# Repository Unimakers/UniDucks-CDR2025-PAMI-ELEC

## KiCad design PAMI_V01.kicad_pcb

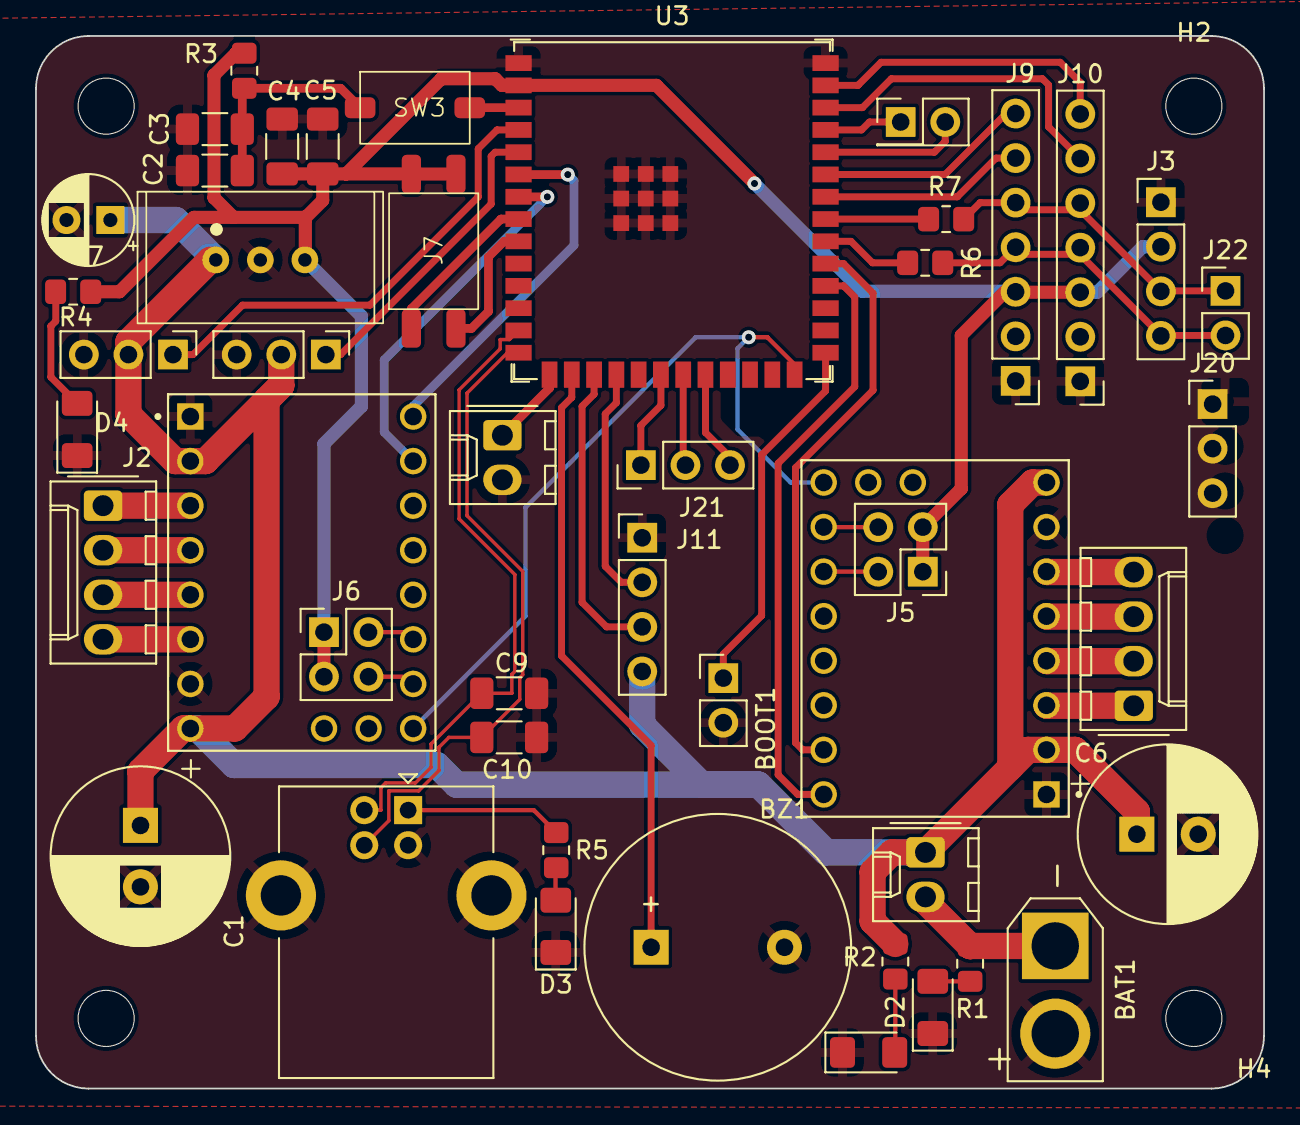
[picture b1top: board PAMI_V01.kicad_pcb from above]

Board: 2 copper layers, 70.0 x 60.0 mm, 50 parts (0 on the bottom side), 52 nets.

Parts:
BAT1: Conn; AMASS_XT30U-F_1x02_P5.0mm_Vertical
BOOT1: Conn; PinHeader_1x02_P2.54mm_Vertical
BZ1: Buzzer; Buzzer_15x7.5RM7.6
C1, C6: 100uF; CP_Radial_D10.0mm_P3.50mm
C2, C5: 0.1uF; C_1206_3216Metric_Pad1.33x1.80mm_HandSolder
C3, C9, C10: TBD; C_1206_3216Metric_Pad1.33x1.80mm_HandSolder
C4: 22uF; C_1206_3216Metric_Pad1.33x1.80mm_HandSolder
C7: 10uF; CP_Radial_D5.0mm_P2.50mm
D1, D2, D3, D4: LED_Small; LED_1206_3216Metric_Pad1.42x1.75mm_HandSolder
H1, H2, H3, H4: MountingHole; MountingHole_3.2mm_M3
J1, J2: Conn_01x04; Molex_KK-254_AE-6410-04A_1x04_P2.54mm_Vertical
J3: Conn_OLED_Screen; PinHeader_1x04_P2.54mm_Vertical
J4: USB_B; USB_B_Lumberg_2411_02_Horizontal
J5, J6: Conn_02x02_Odd_Even; PinHeader_2x02_P2.54mm_Vertical
J7: PAMI_Type; WS-DISV
J8: Conn_01x02; PinHeader_2x01_P2.54mm_Vertical
J9, J10: Conn_01x07; PinHeader_1x07_P2.54mm_Vertical
J11: Conn_HC_SR04; PinHeader_1x04_P2.54mm_Vertical
J20, J21: Conn_01x03; PinHeader_1x03_P2.54mm_Vertical
J22: Conn_01x02; PinHeader_1x02_P2.54mm_Vertical
M1, M2: Motor_Servo; PinHeader_1x03_P2.54mm_Vertical
R1, R2, R4, R5: R_Small; R_0805_2012Metric_Pad1.20x1.40mm_HandSolder
R3: TBD; R_0805_2012Metric_Pad1.20x1.40mm_HandSolder
R6, R7: 220; R_0805_2012Metric_Pad1.20x1.40mm_HandSolder
SW1: TRT; Molex_KK-254_AE-6410-02A_1x02_P2.54mm_Vertical
SW2: BAU; Molex_KK-254_AE-6410-02A_1x02_P2.54mm_Vertical
SW3: EN; WS-TASV 434
U1, U2: TMC2209_SILENTSTEPSTICK; MODULE_TMC2209_SILENTSTEPSTICK
U3: ESP32-S3-WROOM-1; ESP32-S3-WROOM-1U
U5: TSR_2-2433; Traco 2- 24xx

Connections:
+3.3V: C4.2, C5.2, J3.2, J5.1, J5.3, J6.1, J6.3, J7.1, J7.2, J9.3, J10.3, R3.1, R4.2, U3.2 (3V3), U5.3 (VO)
+5V: C1.1, C6.1, C7.1, J11.4, M1.2 (+), M2.2 (+), R2.1, SW2.1 (A), U1.2 (VIO), U1.8 (VM), U2.2 (VIO), U2.8 (VM), U5.1 (VI)
+BATT: BAT1.1, R1.1, SW2.2 (B)
/D+: C10.2, J4.3 (D+), U3.14 (GPIO20/U1CTS/ADC2_CH9/CLK_OUT1/USB_D+)
/D-: C9.2, J4.2 (D-), U3.13 (GPIO19/U1RTS/ADC2_CH8/CLK_OUT2/USB_D-)
GND: BAT1.2, BOOT1.2, BZ1.2 (-), C1.2, C2.1, C3.2, C4.1, C5.1, C6.2, C7.2, C9.1, C10.1, D1.1 (K), D2.1 (K), D3.1 (K), D4.1 (K), J3.1, J4.4 (GND), J4.5 (Shield), J9.1, J10.1, J11.1, M1.3 (-), M2.3 (-), SW1.2 (B), U1.1 (GND), U1.7 (GND), U2.1 (GND), U2.7 (GND), U3.1 (GND), U3.40 (GND), U3.41 (GND), U5.2 (GND)
GPIO1: U1.16 (~EN), U2.16 (~EN), U3.26 (GPIO45)
GPIO1LASER: J9.7, U3.35 (MTMS/GPIO42)
GPIO1LASER2: J10.7, U3.39 (GPIO1/TOUCH1/ADC1_CH0)
GPIO4: M1.1 (PWM), U3.4 (GPIO4/TOUCH4/ADC1_CH3)
GPIO5: M2.1 (PWM), U3.5 (GPIO5/TOUCH5/ADC1_CH4)
GPIO6: U2.9 (DIR), U3.6 (GPIO6/TOUCH6/ADC1_CH5)
GPIO7: U2.10 (STEP), U3.7 (GPIO7/TOUCH7/ADC1_CH6)
GPIO9: J11.3, U3.17 (GPIO9/TOUCH9/ADC1_CH8/FSPIHD/SUBSPIHD)
GPIO10: J11.2, U3.18 (GPIO10/TOUCH10/ADC1_CH9/FSPICS0/FSPIIO4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)
GPIO12: J21.1, U3.20 (GPIO12/TOUCH12/ADC2_CH1/FSPICLK/FSPIIO6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)
GPIO13: J21.2, U3.21 (GPIO13/TOUCH13/ADC2_CH2/FSPIQ/FSPIIO7/S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)
GPIO14: J21.3, U3.22 (GPIO14/TOUCH14/ADC2_CH3/FSPIWP/FSPIDQS/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)
GPIO15: J7.4, U3.8 (GPIO15/U0RTS/ADC2_CH4/XTAL_32K_P)
GPIO16: J7.3, U3.9 (GPIO16/U0CTS/ADC2_CH5/XTAL_32K_N)
GPIO35: U1.9 (DIR), U3.30 (SPIDQS/GPIO37/FSPIQ/SUBSPIQ)
GPIO36: U1.10 (STEP), U3.31 (GPIO38/FSPIWP/SUBSPIWP)
unnamed: BOOT1.1, U3.27 (GPIO0/BOOT)
unnamed: BZ1.1 (+), U3.16 (GPIO46)
unnamed: D1.2 (A), R1.2
unnamed: D2.2 (A), R2.2
unnamed: D3.2 (A), R5.2
unnamed: D4.2 (A), R4.1
unnamed: J1.1, U1.3 (M1B)
unnamed: J1.2, U1.4 (M1A)
unnamed: J1.3, U1.5 (M2A)
unnamed: J1.4, U1.6 (M2B)
unnamed: J2.1, U2.3 (M1B)
unnamed: J2.2, U2.4 (M1A)
unnamed: J2.3, U2.5 (M2A)
unnamed: J2.4, U2.6 (M2B)
unnamed: J4.1 (VBUS), R5.1
unnamed: J5.2, U1.14 (MS2)
unnamed: J5.4, U1.15 (MS1)
unnamed: J6.2, U2.14 (MS2)
unnamed: J6.4, U2.15 (MS1)
unnamed: J8.1, U3.37 (U0TXD/GPIO43/CLK_OUT1)
unnamed: J8.2, U3.36 (U0RXD/GPIO44/CLK_OUT2)
unnamed: SW1.1 (A), U3.15 (GPIO3/TOUCH3/ADC1_CH2)
unnamed: C2.2, C3.1, R3.2, SW3.1 (A)
unnamed: SW3.2 (B), U3.3 (EN)
unnamed: R6.1, U3.32 (MTCK/GPIO39/CLK_OUT3/SUBSPICS1)
unnamed: R7.2, U3.33 (MTDO/GPIO40/CLK_OUT2)
SCL: J3.3, J9.5, J10.5, J22.1, R7.1
SDA: J3.4, J9.4, J10.4, J22.2, R6.2
XSHUT: J9.6, U3.34 (MTDI/GPIO41/CLK_OUT1)
XSHUT2: J10.6, U3.38 (GPIO2/TOUCH2/ADC1_CH1)

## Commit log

2025-02-17 Create main
2025-02-17 Update main
2025-02-17 upload 1
2025-02-17 upload 2
2025-02-17 upload 3
2025-02-17 upload 4
2025-02-17 upload 5
2025-02-17 upload 6
2025-02-17 upload 6.1
2025-02-17 upload 6.2
2025-02-17 upload 7
2025-02-17 upload 7.1
2025-02-17 upload 7.2
2025-03-01 updating kicad files
2025-03-05 Unishape PAMI board V2
